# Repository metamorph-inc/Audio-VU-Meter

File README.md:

# Audio-VU-Meter
_author: Will Knight_

This Metamorphosys design project captures a simple audio VU meter circuit. A microphone on the board picks up ambient audio, and a column of colored LEDs illuminates depending on the ambient sound level. It uses jumpers to connect to an Arduino board, where audio processing and LED control takes place.

## Architecture

## Analysis
_what test benches to run, and what you'll see_

## Caveats
_assumptions, hacks, etc_

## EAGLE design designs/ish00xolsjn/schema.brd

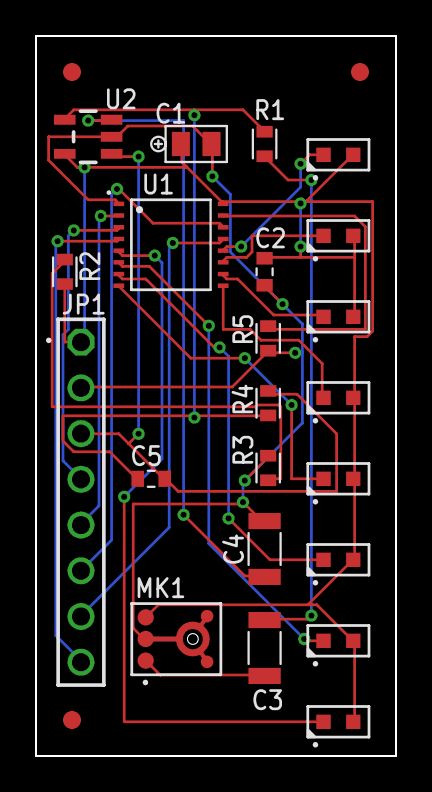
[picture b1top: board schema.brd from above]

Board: 2 copper layers, 20.0 x 40.0 mm, 25 parts (0 on the bottom side), 22 nets.

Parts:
C1: C_TANT_0805; AVX-0805
C2, C5: C0603
C3, C4: C1206
D1, D2, D3, D4, D5, D6, D7, D8: LED-0603-KINGBRIGHT; 0603-LED-KINGBRIGHT
FD1, FD2, FD3: FIDUCIAL_1MM
JP1: 1X8-HEADER
MK1: INMP401
R1, R2, R3, R4, R5: RESISTOR_0603; R_0603
U1: STP08DP05TTRSTP08DP05TTR; STP08DP05TTR
U2: OPA344; SOT23-5

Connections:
unnamed: C1.POS, C2.2, D1.P$2, D2.P$2, D3.P$2, D4.P$2, D5.P$2, D6.P$2, D7.P$2, D8.P$2, JP1.1, MK1.5, R2.P$1, U1.P$16, U2.5
unnamed: C1.NEG, C2.1, C4.2, JP1.2, MK1.2, MK1.4, MK1.6, R3.P$2, R5.P$1, U1.P$1, U2.2
unnamed: C3.2, R1.P$1
unnamed: C3.1, MK1.1
unnamed: C4.1, U2.3
unnamed: C5.1, R1.P$2, R4.P$1, U2.4
unnamed: C5.2, JP1.3, R4.P$2, U2.1
unnamed: D1.P$1, U1.P$5
unnamed: D2.P$1, U1.P$6
unnamed: D3.P$1, U1.P$7
unnamed: D4.P$1, U1.P$8
unnamed: D5.P$1, U1.P$9
unnamed: D6.P$1, U1.P$10
unnamed: D7.P$1, U1.P$11
unnamed: D8.P$1, U1.P$12
unnamed: JP1.8, U1.P$4
unnamed: JP1.6, U1.P$14
unnamed: JP1.4, U1.P$3
unnamed: JP1.5, U1.P$2
unnamed: JP1.7, U1.P$13
unnamed: R2.P$2, R3.P$1
unnamed: R5.P$2, U1.P$15

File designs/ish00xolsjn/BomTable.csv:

,,Design Name:,VUmeter
,,Pricing Timestamp:,"Wednesday, February 11, 2015 3:59 PM"
,,Cost per Unit (based on 1 unit):,$5.43

"Item #",Qty,"Reference Designator",Manufacturer,"Manufacturer Part #",Description,Package,"Supplier 1","Supplier 1 SKU","Supplier 1 Price/Unit","Supplier 1 Extended Price",Notes
1,1,R4,Rohm,MCR03ERTJ104,"RES SMD 100K OHM 5% 1/10W 0603",,Digi-Key,RHM100KCGCT-ND,0.1,0.1,
2,2,"R3, 
R2",Rohm,MCR03ERTJ103,"CHIP RESISTOR 0603 10K OHM 5%",,Digi-Key,RHM10KCGDKR-ND,0.1,0.2,
3,1,D8,Kingbright,APT1608EC,SMTLEDASSY20MARED0603SM,'0603,Mouser,604-APT1608EC,0.13,0.13,"Lead Free, RoHS Compliant"
4,1,C2,Kemet,C0603C104K8RACTU,"CAP CER 0.1UF 10V 10% X7R 0603",'0603,Newark,77R3552,0.003,0.003,"R, RoHS Compliant"
5,1,FD3,,,,,,,,,
6,1,FD1,,,,,,,,,
7,1,C1,"AVX Interconnect / Elco",TAJP106K010RNJ,"CAP TANT 10UF 10V 10% 0805",'0805,Newark,65M4924,0.413,0.413,"Lead Free, RoHS Compliant"
8,2,"D6, 
D7",Kingbright,APT1608YC,"1.6X0.8MM YELLOW SMD LED",'0603,"Allied Electronics",'70062843,0.134,0.268,"Lead Free, RoHS Compliant"
9,5,"D3, 
D2, 
D4, 
D5, 
D1",Kingbright,APT1608SGC,"1.6X0.8MM GREEN SMD LED",'0603,"Future Electronics",APT1608SGC,0.0429,0.2145,"Lead Free, RoHS Compliant"
10,1,C5,"AVX Interconnect / Elco",0603YC101KAT2A,"CAP CER 100PF 16V 10% X7R 0603",'0603,Newark,94W2848,0.032,0.032,"Lead Free, RoHS Compliant"
11,1,C4,Murata,GRM31MR61C105KA01L,"CAP,1UF,10%,16V,X5R,CERAM",'1206,Digi-Key,490-1810-1-ND,0.28,0.28,"Lead Free, RoHS Compliant, Lifecycle Status Active"
12,1,C3,Samsung,CL31A475KPHNNNE,"CAP CER 4.7UF 10V 10% X5R 1206",'1206,Digi-Key,1276-1809-6-ND,0.25,0.25,"Lead Free, RoHS Compliant"
13,1,JP1,,,,,,,,,
14,1,R5,Rohm,MCR03ERTJ182,"RES SMD 1.8K OHM 5% 1/10W 0603",,Digi-Key,RHM1.8KCGDKR-ND,0.1,0.1,
15,1,R1,Rohm,MCR03ERTJ152,"RES SMD 1.5K OHM 5% 1/10W 0603",,Digi-Key,RHM1.5KCGCT-ND,0.1,0.1,
16,1,FD2,,,,,,,,,
17,1,U2,"Texas Instruments",OPA344UA,"IC OPAMP GP 1MHZ RRO 8SOIC",SOIC-8,Arrow,OPA344UA,0.8914,0.8914,"Lead Free, RoHS Compliant, Lifecycle Status Active"
18,1,MK1,InvenSense,INMP401ACEZ,"Omnidirectional Analog MEMS Microphone",,"Component Distributors Inc.",INMP401ACEZ,1.62,1.62,
19,1,U1,STMicroelectronics,STP08DP05TTR,"IC LED DRIVER LINEAR 16-TSSOP",,Newark,57P1838,0.829,0.829,"Lead Free, RoHS Compliant, Lifecycle Status Active"

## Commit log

2015-02-05 Initial model check-in
2015-02-17 Update with final details for manufacturing
2015-02-17 Added STEP files for components in VUMeter assembly. Added CyPhy2CADPCB test bench.
2015-03-12 CT-39. Replaced all components with standard library components in morph-component repo. Didn't touch connectors at the connector assembly levels.
2015-03-18 Add missing template file
2015-03-18 Migrate constraints to use new colon-delimited range style
2015-03-18 Remove lbr content that caused parsing errors (<library> element couldn't be found be deserializer)
2015-03-18 Migrate to use new origin-based layout constraint specification
